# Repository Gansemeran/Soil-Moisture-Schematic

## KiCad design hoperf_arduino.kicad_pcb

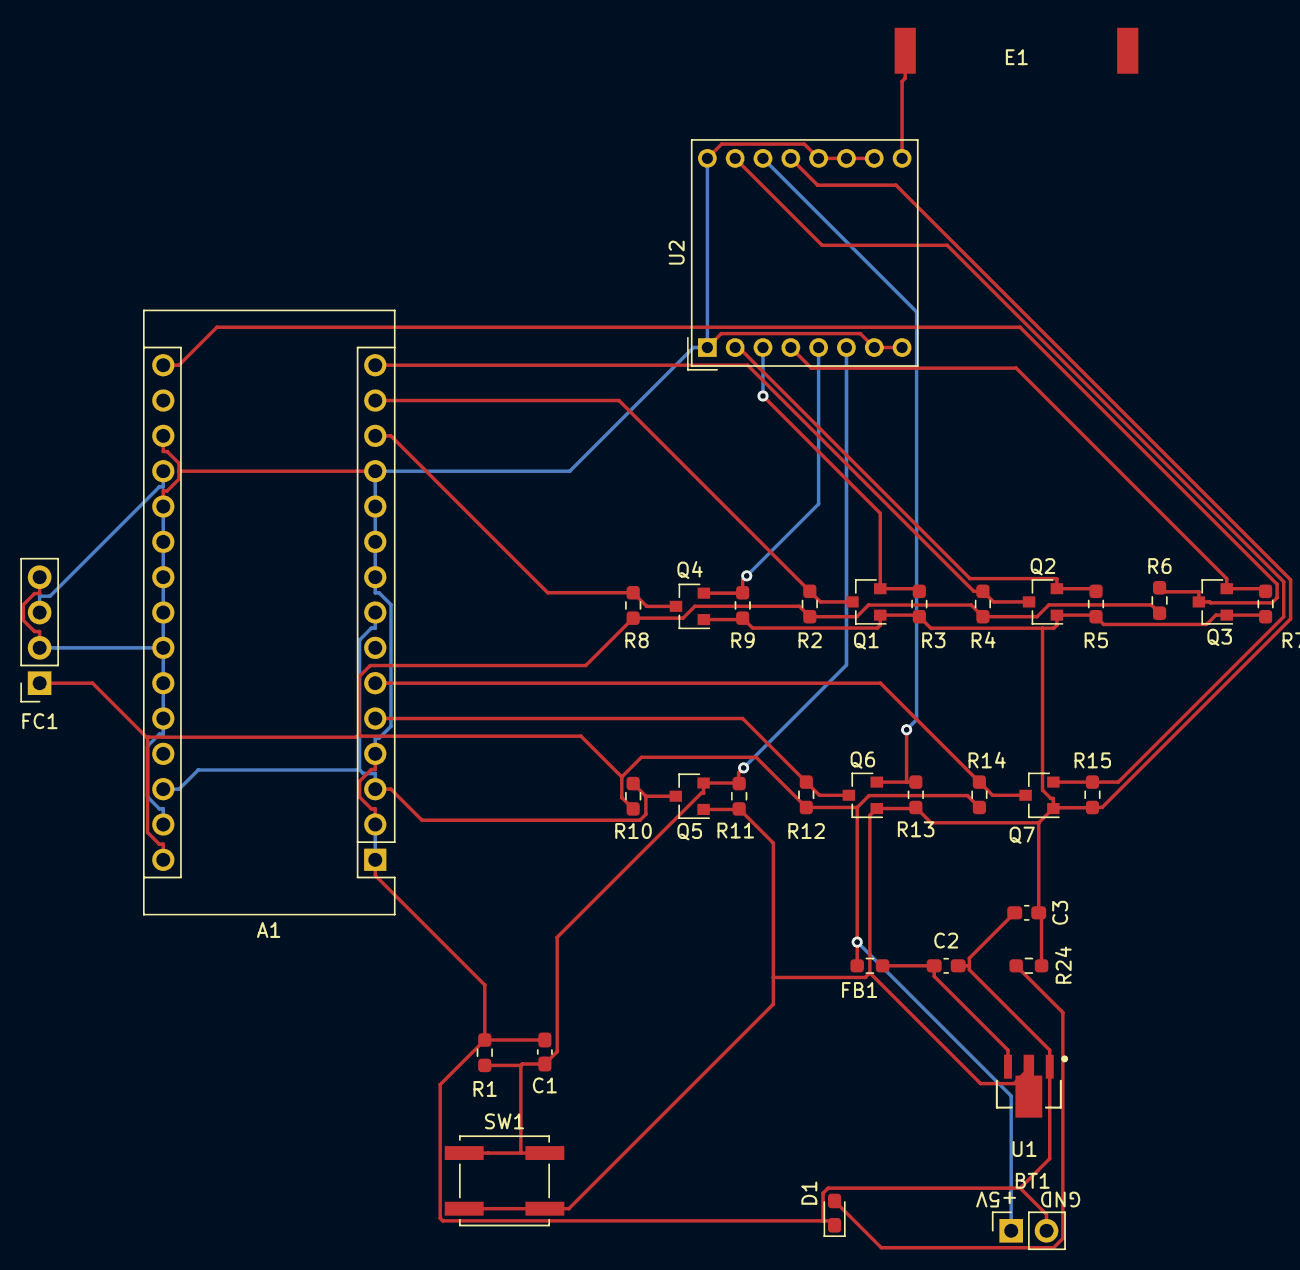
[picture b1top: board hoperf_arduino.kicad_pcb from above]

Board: 2 copper layers, 35 parts (0 on the bottom side), 21 nets.

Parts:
A1: Arduino_Nano_v3.x; Arduino_Nano
BT1: Battery_Cell; PinSocket_1x02_P2.54mm_Vertical
C1: 1uF; C_0603_1608Metric_Pad1.08x0.95mm_HandSolder
C2: 10uF; C_0603_1608Metric_Pad1.08x0.95mm_HandSolder
C3: 22uF; C_0603_1608Metric_Pad1.08x0.95mm_HandSolder
D1: LED; LED_0603_1608Metric_Pad1.05x0.95mm_HandSolder
E1: ANT-916-CHP-T; ant-916-chp-t
FB1: Ferrite_Bead_Small; R_0603_1608Metric_Pad0.98x0.95mm_HandSolder
FC1: FC-28; PinSocket_1x04_P2.54mm_Vertical
Q1, Q2, Q3, Q4, Q5, Q6, Q7: DMN6140L; SOT-23
R1, R2, R3, R4, R5, R6, R7, R8, R9, R10, R11, R12, R13, R14, R15: 10k; R_0603_1608Metric_Pad0.98x0.95mm_HandSolder
R24: 330; R_0603_1608Metric_Pad0.98x0.95mm_HandSolder
SW1: SW_SPST; SW_Push_1P1T_NO_CK_KSC7xxJ
U1: AZ1117-3.3; Diodes_Inc.-SOT89-03_2017-0-MFG
U2: RFM95W-915S2; HOPERF_RFM9XW_THT

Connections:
+3V3: C3.1, Q1.1, Q2.1, Q3.1, Q4.1, Q5.1, Q6.1, Q7.1, R3.1, R5.1, R7.1, R9.1, R11.1, R13.1, R15.1, R24.2, SW1.1, U1.2, U2.13
+5V: A1.30, BT1.1, FB1.2, FC1.1, R2.1, R4.1, R6.1, R8.1, R10.1, R12.1, R14.1
/FC_A0: A1.19, FC1.3
/H_CS: A1.13, Q4.3, R8.2
/H_DIO0: A1.5, Q6.3, R12.2
/H_DIO1: A1.6, Q7.3, R14.2
/H_MISO: A1.15, Q2.3, R4.2
/H_MOSI: A1.14, Q1.3, R2.2
/H_RESET: A1.3, A1.8, A1.28, Q5.3, R10.2
/H_SCK: A1.16, Q3.3, R6.2
/L_CS: Q4.2, R9.2, U2.5
/L_DIO0: Q6.2, R13.2, U2.14
/L_DIO1: Q7.2, R15.2, U2.15
/L_MISO: Q2.2, R5.2, U2.2
/L_MOSI: Q1.2, R3.2, U2.3
/L_RESET: C1.1, Q5.2, R1.1, R11.2, SW1.2, U2.6
/L_SCK: Q3.2, R7.2, U2.4
GND: A1.1, A1.2, A1.4, A1.9, A1.10, A1.11, A1.12, A1.18, A1.20, A1.21, A1.22, A1.23, A1.24, A1.25, A1.26, A1.29, BT1.2, C1.2, C2.2, C3.2, D1.1, FC1.2, FC1.4, R1.2, U1.1, U2.1, U2.7, U2.8, U2.10, U2.11, U2.12, U2.16
unnamed: C2.1, FB1.1, U1.3
unnamed: D1.2, R24.1
unnamed: E1.1, U2.9

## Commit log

2021-06-22 init
2021-06-24 update sch and added routed pcb
2021-06-24 remove unncessary parts, update sch
2021-06-24 add gerber files
